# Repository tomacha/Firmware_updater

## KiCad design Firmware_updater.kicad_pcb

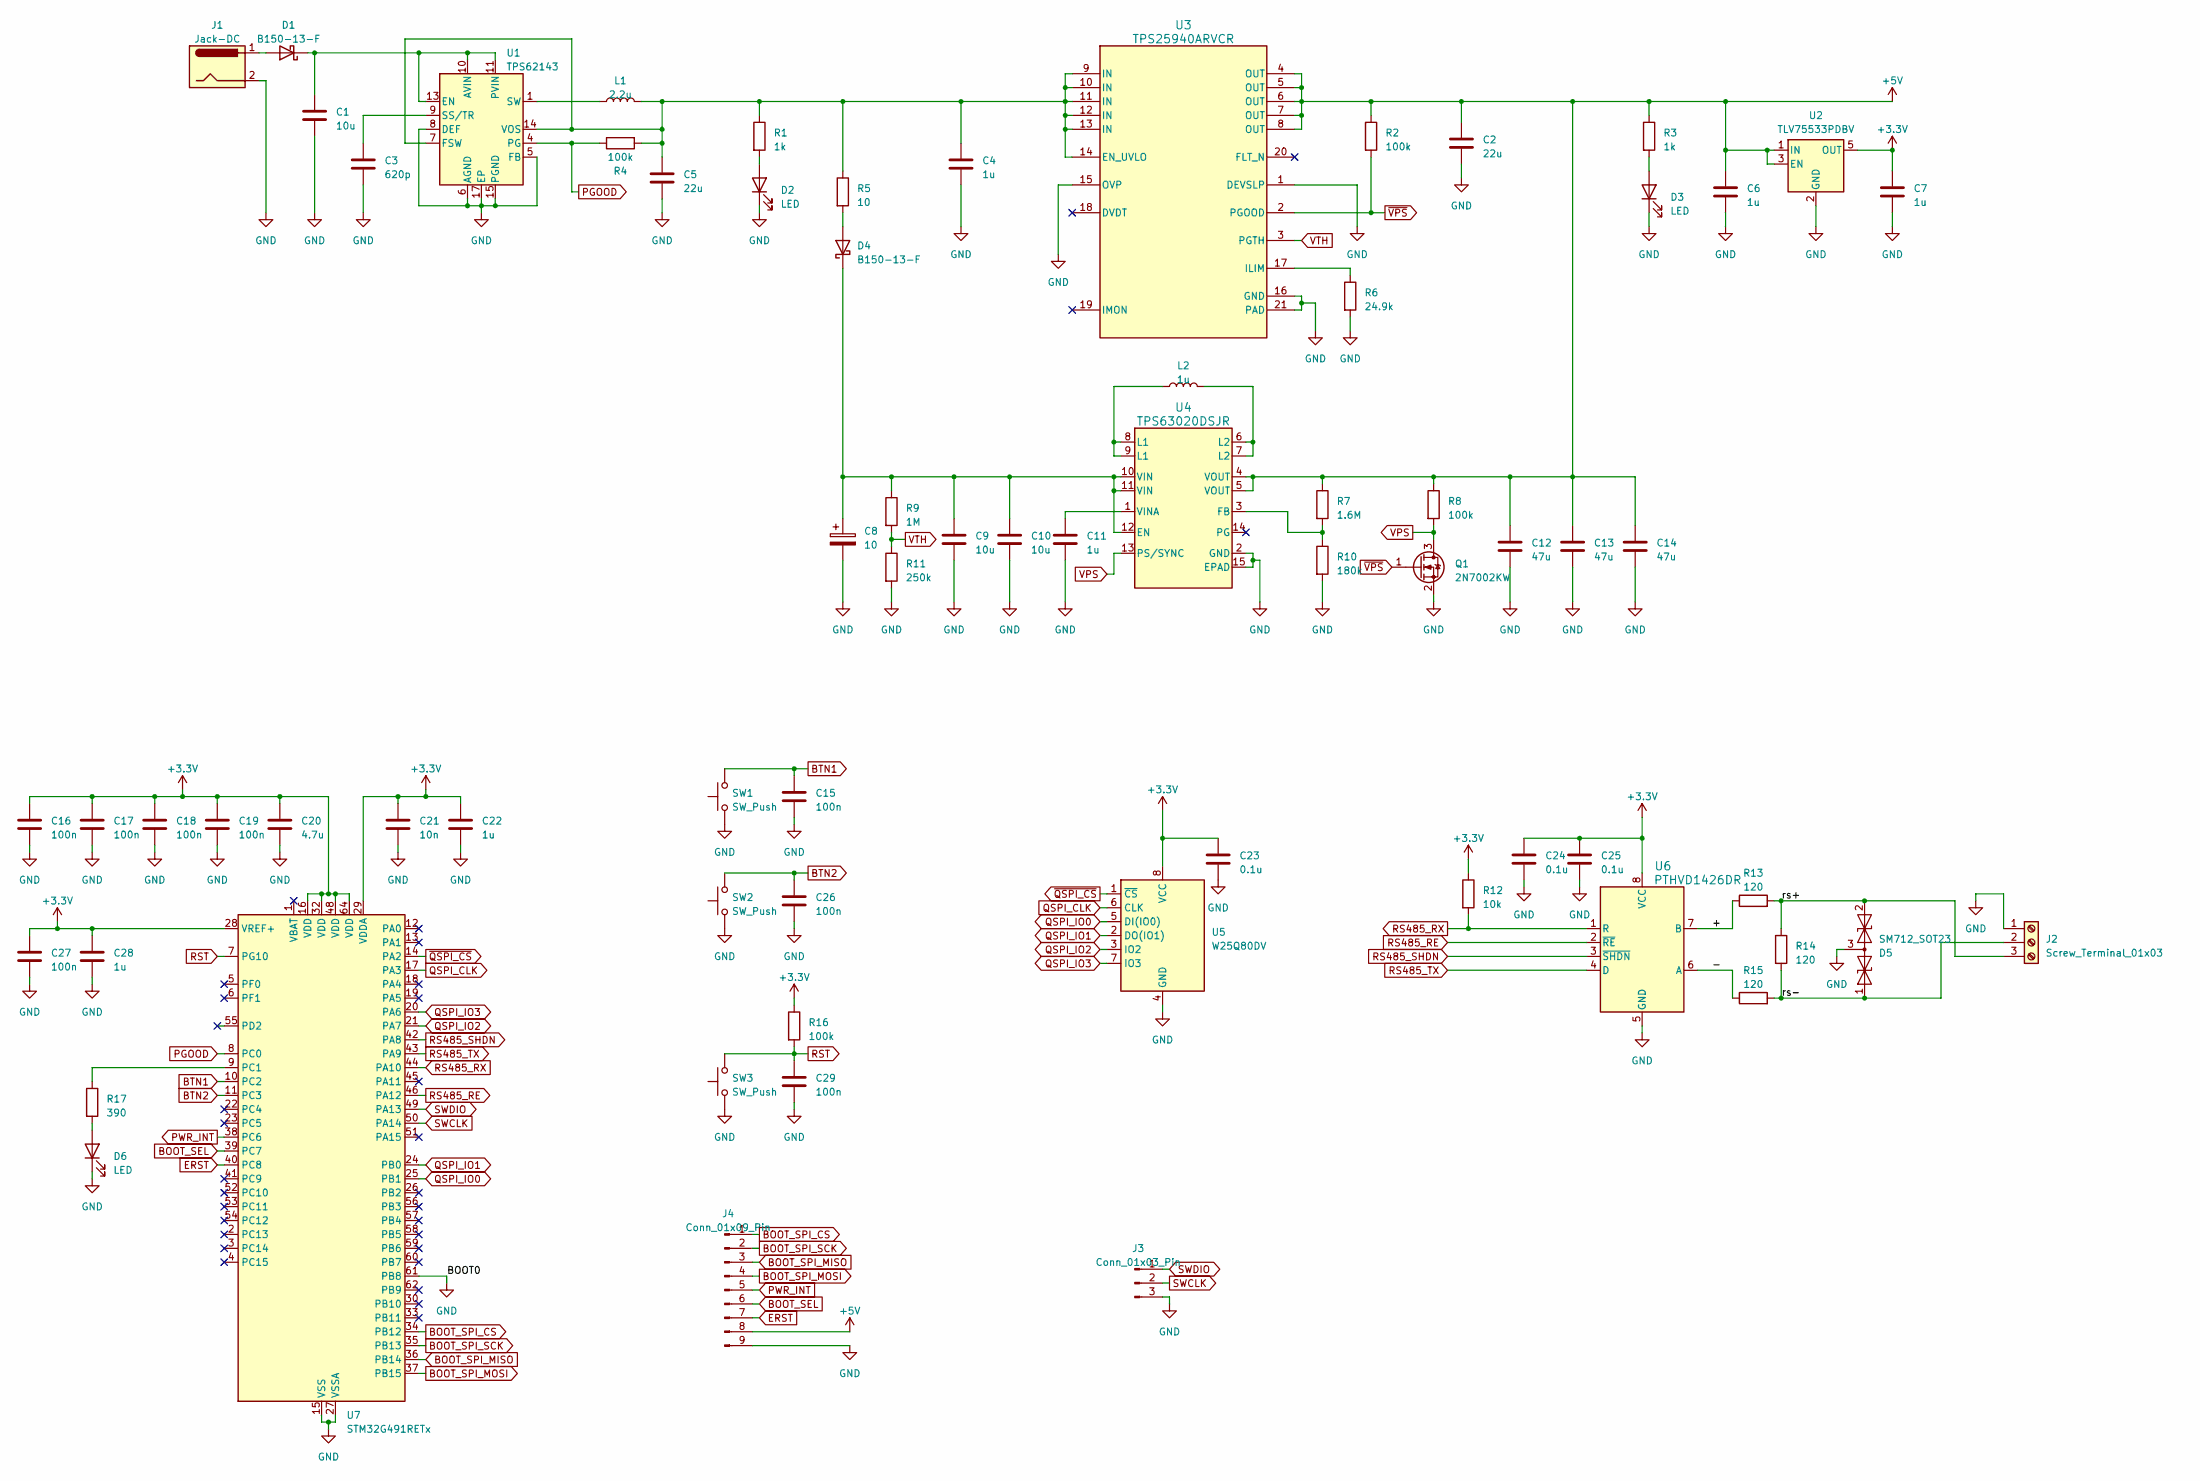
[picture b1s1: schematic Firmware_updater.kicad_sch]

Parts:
C1, C9, C10: 10u; C_0805_2012Metric_Pad1.18x1.45mm_HandSolder
C2, C5: 22u; C_0805_2012Metric_Pad1.18x1.45mm_HandSolder
C3: 620p; C_0805_2012Metric_Pad1.18x1.45mm_HandSolder
C4, C6, C7, C11, C22, C28: 1u; C_0805_2012Metric_Pad1.18x1.45mm_HandSolder
C8: 10; TerminalBlock_bornier-2_P5.08mm
C12, C13, C14: 47u; C_0805_2012Metric_Pad1.18x1.45mm_HandSolder
C15, C16, C17, C18, C19, C26, C27, C29: 100n; C_0805_2012Metric_Pad1.18x1.45mm_HandSolder
C20: 4.7u; C_0805_2012Metric_Pad1.18x1.45mm_HandSolder
C21: 10n; C_0805_2012Metric_Pad1.18x1.45mm_HandSolder
C23, C24, C25: 0.1u; C_0805_2012Metric_Pad1.18x1.45mm_HandSolder
D1, D4: B150-13-F; D_SMA
D2, D3, D6: LED; LED_0805_2012Metric_Pad1.15x1.40mm_HandSolder
D5: SM712_SOT23; SOT-23
J1: Jack-DC; BarrelJack_Kycon_KLDX-0202-xC_Horizontal
J2: Screw_Terminal_01x03; TerminalBlock_bornier-3_P5.08mm
J3: Conn_01x03_Pin; PinHeader_1x03_P2.54mm_Vertical
J4: Conn_01x09_Pin; PinHeader_1x09_P2.54mm_Vertical
L1: 2.2u; L_Coilcraft_XxL4040
L2: 1u; L_Coilcraft_XxL4040
Q1: 2N7002KW; SOT-23
R1, R3: 1k; R_0805_2012Metric_Pad1.20x1.40mm_HandSolder
R2, R4, R8, R16: 100k; R_0805_2012Metric_Pad1.20x1.40mm_HandSolder
R5: 10; R_2512_6332Metric_Pad1.40x3.35mm_HandSolder
R6: 24.9k; R_0805_2012Metric_Pad1.20x1.40mm_HandSolder
R7: 1.6M; R_0805_2012Metric_Pad1.20x1.40mm_HandSolder
R9: 1M; R_0805_2012Metric_Pad1.20x1.40mm_HandSolder
R10: 180k; R_0805_2012Metric_Pad1.20x1.40mm_HandSolder
R11: 250k; R_0805_2012Metric_Pad1.20x1.40mm_HandSolder
R12: 10k; R_0805_2012Metric_Pad1.20x1.40mm_HandSolder
R13, R14, R15: 120; R_0805_2012Metric_Pad1.20x1.40mm_HandSolder
R17: 390; R_0805_2012Metric_Pad1.20x1.40mm_HandSolder
SW1, SW2, SW3: SW_Push; SW_Push_1P1T_XKB_TS-1187A
U1: TPS62143; VQFN-16-1EP_3x3mm_P0.5mm_EP1.68x1.68mm_ThermalVias
U2: TLV75533PDBV; SOT-23-5
U3: TPS25940ARVCR; RVC0020A
U4: TPS63020DSJR; DSJ14_2P85X1P58
U5: W25Q80DV; SOIC-8_5.23x5.23mm_P1.27mm
U6: PTHVD1426DR; SOIC_1426DR_TEX
U7: STM32G491RETx; LQFP-64_10x10mm_P0.5mm

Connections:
+3.3V: C7.1, C16.1, C17.1, C18.1, C19.1, C20.1, C21.1, C22.1, C23.1, C24.1, C25.1, C27.1, C28.1, R12.1, R16.1, U2.5 (OUT), U5.8 (VCC), U6.8 (VCC), U7.16 (VDD), U7.28 (VREF+), U7.29 (VDDA), U7.32 (VDD), U7.48 (VDD), U7.64 (VDD)
+5V: C2.1, C6.1, C12.1, C13.1, C14.1, J4.8, R2.1, R3.1, R7.1, R8.1, U2.1 (IN), U2.3 (EN), U3.4 (OUT), U3.5 (OUT), U3.6 (OUT), U3.7 (OUT), U3.8 (OUT), U4.4 (VOUT), U4.5 (VOUT)
/+: R13.1, U6.7 (B)
/-: R15.1, U6.6 (A)
/rs+: D5.2 (A2), J2.3, R13.2, R14.1
/rs-: D5.1 (A1), J2.2, R14.2, R15.2
BOOT_SEL: J4.6, U7.39 (PC7)
BOOT_SPI_CS: J4.1, U7.34 (PB12)
BOOT_SPI_MISO: J4.3, U7.36 (PB14)
BOOT_SPI_MOSI: J4.4, U7.37 (PB15)
BOOT_SPI_SCK: J4.2, U7.35 (PB13)
BTN1: C15.1, SW1.2, U7.10 (PC2)
BTN2: C26.1, SW2.2, U7.11 (PC3)
ERST: J4.7, U7.40 (PC8)
GND: C1.2, C2.2, C3.2, C4.2, C5.2, C6.2, C7.2, C8.2, C9.2, C10.2, C11.2, C12.2, C13.2, C14.2, C15.2, C16.2, C17.2, C18.2, C19.2, C20.2, C21.2, C22.2, C23.2, C24.2, C25.2, C26.2, C27.2, C28.2, C29.2, D2.1 (K), D3.1 (K), D5.3 (common), D6.1 (K), J1.2, J2.1, J3.3, J4.9, Q1.2 (S), R6.2, R10.2, R11.2, SW1.1, SW2.1, SW3.1, U1.5 (FB), U1.6 (AGND), U1.8 (DEF), U1.15 (PGND), U1.16 (PGND), U1.17 (EP), U2.2 (GND), U3.1 (DEVSLP), U3.15 (OVP), U3.16 (GND), U3.21 (PAD), U4.2 (GND), U4.15 (EPAD), U5.4 (GND), U6.5 (GND), U7.15 (VSS), U7.27 (VSSA), U7.31 (VSS), U7.47 (VSS), U7.61 (PB8), U7.63 (VSS)
unnamed: D1.2 (A), J1.1
unnamed: C1.1, D1.1 (K), U1.10 (AVIN), U1.11 (PVIN), U1.12 (PVIN), U1.13 (EN)
unnamed: D2.2 (A), R1.2
unnamed: D3.2 (A), R3.2
unnamed: D4.2 (A), R5.2
unnamed: C8.1, C9.1, C10.1, D4.1 (K), R9.1, U4.10 (VIN), U4.11 (VIN), U4.12 (EN)
unnamed: D6.2 (A), R17.2
unnamed: L1.1, U1.1 (SW), U1.2 (SW), U1.3 (SW)
unnamed: L2.1, U4.8 (L1), U4.9 (L1)
unnamed: L2.2, U4.6 (L2), U4.7 (L2)
unnamed: C4.1, C5.1, L1.2, R1.1, R4.2, R5.1, U1.7 (FSW), U1.14 (VOS), U3.9 (IN), U3.10 (IN), U3.11 (IN), U3.12 (IN), U3.13 (IN), U3.14 (EN_UVLO)
unnamed: C3.1, U1.9 (SS/TR)
unnamed: R6.1, U3.17 (ILIM)
unnamed: R7.2, R10.1, U4.3 (FB)
unnamed: C11.1, U4.1 (VINA)
unnamed: R17.1, U7.9 (PC1)
PGOOD: R4.1, U1.4 (PG), U7.8 (PC0)
PWR_INT: J4.5, U7.38 (PC6)
QSPI_CLK: U5.6 (CLK), U7.17 (PA3)
QSPI_IO0: U5.5 (DI(IO0)), U7.25 (PB1)
QSPI_IO1: U5.2 (DO(IO1)), U7.24 (PB0)
QSPI_IO2: U5.3 (IO2), U7.21 (PA7)
QSPI_IO3: U5.7 (IO3), U7.20 (PA6)
RS485_RE: U6.2 (~RE), U7.46 (PA12)
RS485_RX: R12.2, U6.1 (R), U7.44 (PA10)
RS485_SHDN: U6.3 (~SHDN), U7.42 (PA8)
RS485_TX: U6.4 (D), U7.43 (PA9)
RST: C29.1, R16.2, SW3.2, U7.7 (PG10)
SWCLK: J3.2, U7.50 (PA14)
SWDIO: J3.1, U7.49 (PA13)
VPS: Q1.3 (D), R8.2, U4.13 (PS/SYNC)
VTH: R9.2, R11.1, U3.3 (PGTH)
~QSPI_CS: U5.1 (~CS), U7.14 (PA2)
~VPS: Q1.1 (G), R2.2, U3.2 (PGOOD)

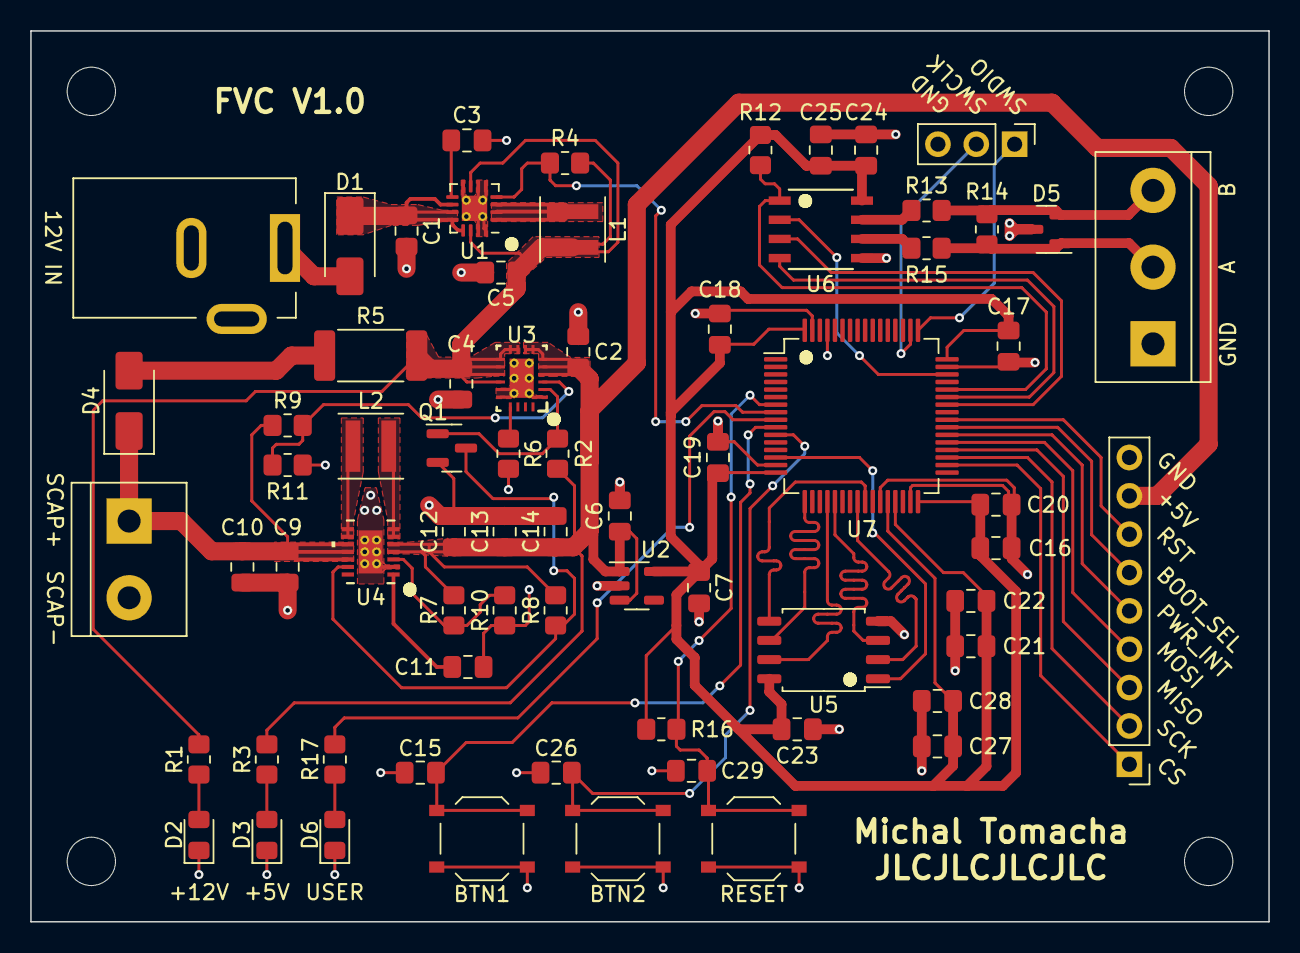
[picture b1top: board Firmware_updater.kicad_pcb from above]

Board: 2 copper layers, 82.0 x 59.0 mm, 69 parts (0 on the bottom side), 49 nets.
